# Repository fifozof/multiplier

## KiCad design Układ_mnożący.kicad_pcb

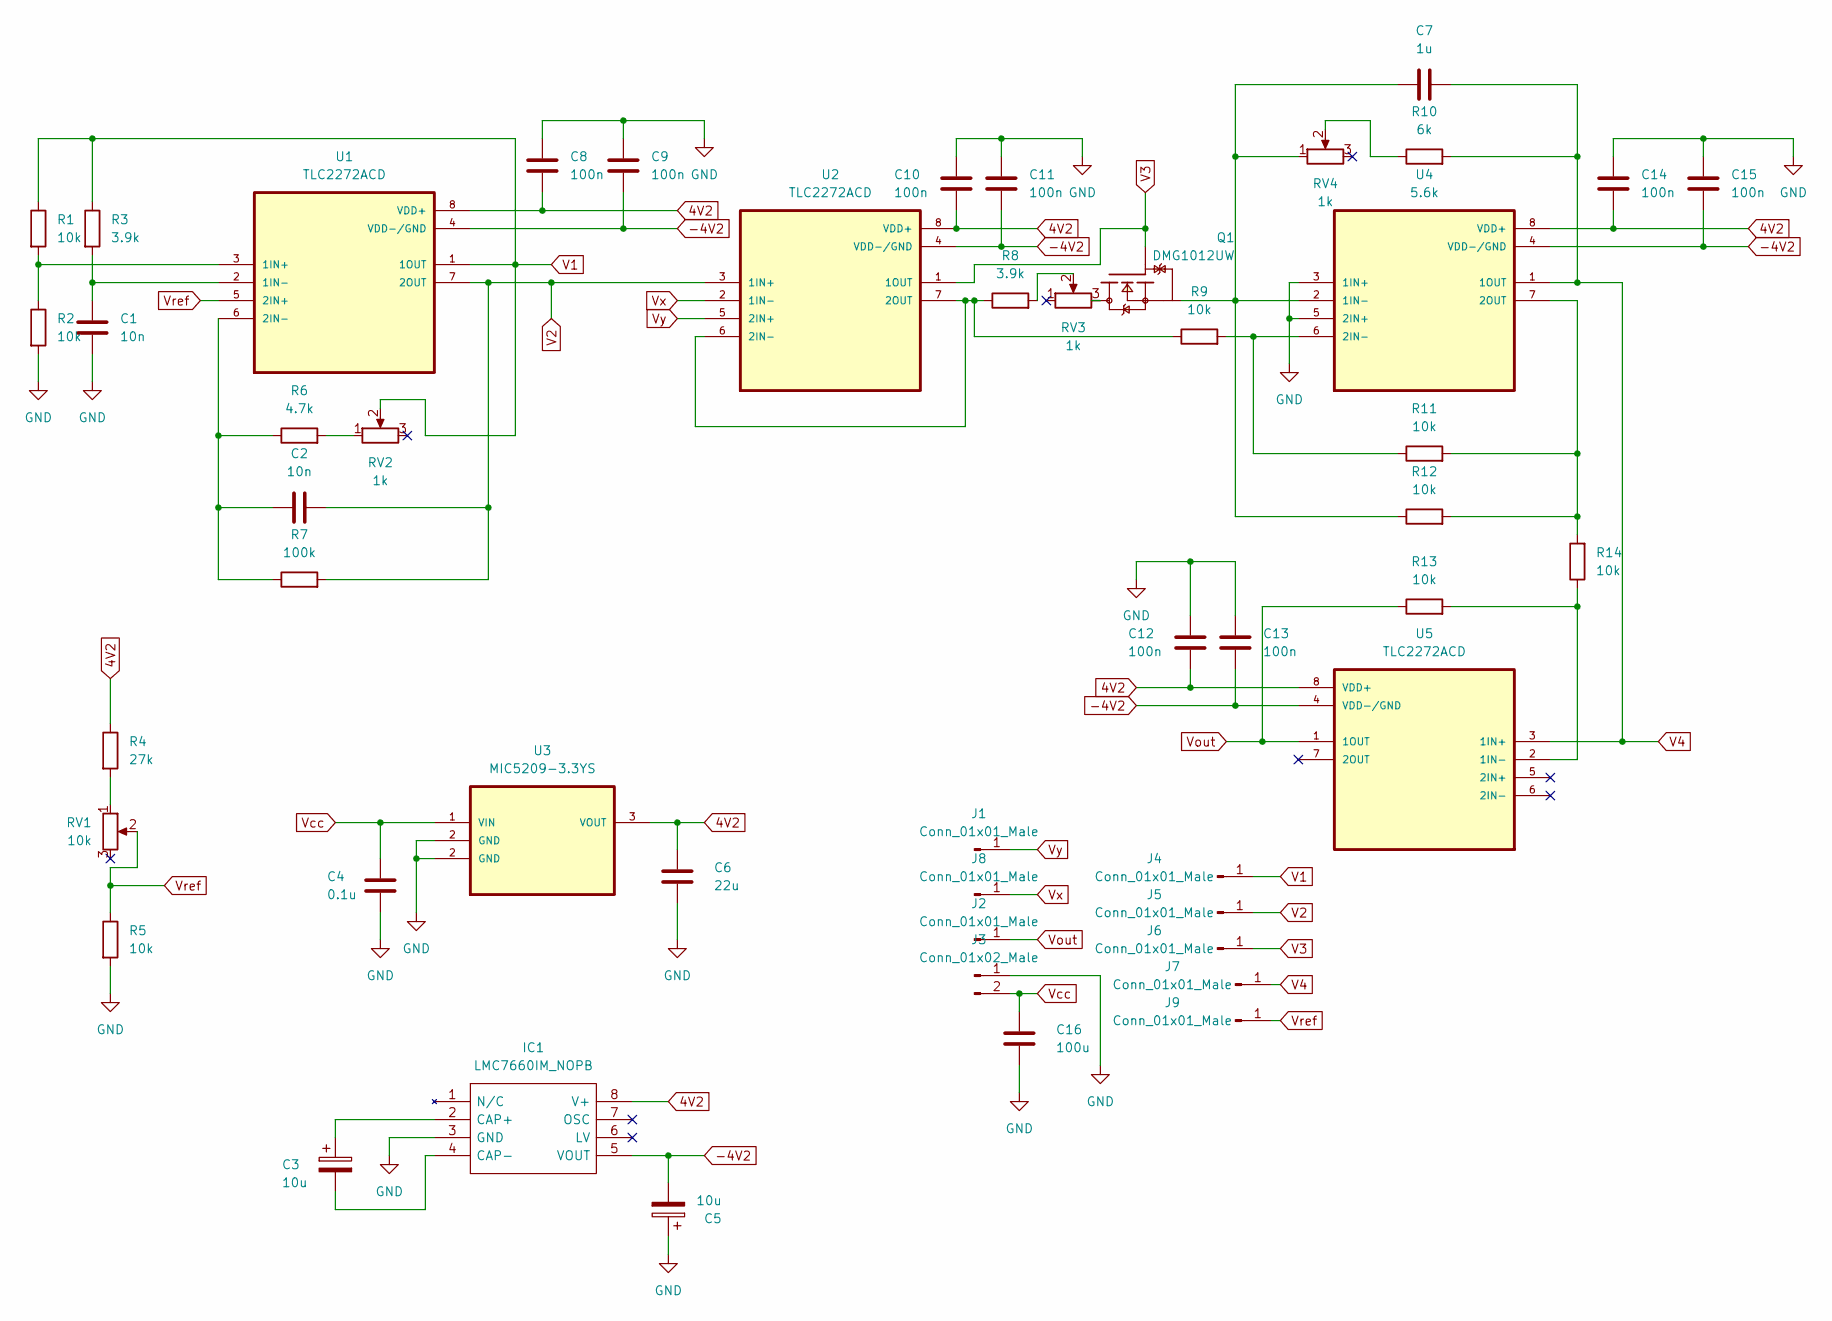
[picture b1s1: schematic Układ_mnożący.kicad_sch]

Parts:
C1, C2: 10n; C_0805_2012Metric_Pad1.18x1.45mm_HandSolder
C3, C5: 10u; C_1206_3216Metric_Pad1.33x1.80mm_HandSolder
C4: 0.1u; C_0805_2012Metric_Pad1.18x1.45mm_HandSolder
C6: 22u; CP_EIA-3528-21_Kemet-B
C7: 1u; C_0805_2012Metric_Pad1.18x1.45mm_HandSolder
C8, C9, C10, C11, C12, C13, C14, C15: 100n; C_0805_2012Metric_Pad1.18x1.45mm_HandSolder
C16: 100u; CP_EIA-3528-21_Kemet-B
IC1: LMC7660IM_NOPB; SOIC127P600X175-8N; Mouser Part Number 926-LMC7660IM/NOPB
J1, J2, J4, J5, J6, J7, J8, J9: Conn_01x01_Male; PinHeader_1x01_P2.54mm_Vertical
J3: Conn_01x02_Male; PinHeader_1x02_P2.54mm_Vertical
Q1: DMG1012UW; SOT323
R1, R2, R5, R9, R11, R12, R13, R14: 10k; R_0805_2012Metric_Pad1.20x1.40mm_HandSolder
R3, R8: 3.9k; R_0805_2012Metric_Pad1.20x1.40mm_HandSolder
R4: 27k; R_0805_2012Metric_Pad1.20x1.40mm_HandSolder
R6: 4.7k; R_0805_2012Metric_Pad1.20x1.40mm_HandSolder
R7: 100k; R_0805_2012Metric_Pad1.20x1.40mm_HandSolder
R10: 6k; R_0805_2012Metric_Pad1.20x1.40mm_HandSolder
RV1: 10k; Potentiometer_ACP_CA6-H2,5_Horizontal
RV2, RV3, RV4: 1k; Potentiometer_ACP_CA6-H2,5_Horizontal
U1, U2, U5: TLC2272ACD; SOIC127P599X175-8N
U3: MIC5209-3.3YS; SOT-223-3_TabPin2
U4: 5.6k; SOIC127P599X175-8N

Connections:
4V2: C6.1, C8.2, C10.2, C12.2, C14.2, IC1.8 (V+), R4.1, U1.8 (VDD+), U2.8 (VDD+), U3.3 (VOUT), U4.8 (VDD+), U5.8 (VDD+)
-4V2: C5.2, C9.2, C11.2, C13.2, C15.2, IC1.5 (VOUT), U1.4 (VDD-/GND), U2.4 (VDD-/GND), U4.4 (VDD-/GND), U5.4 (VDD-/GND)
GND: C1.2, C4.2, C5.1, C6.2, C8.1, C9.1, C10.1, C11.1, C12.1, C13.1, C14.1, C15.1, C16.2, IC1.3 (GND), J3.1, R2.2, R5.2, U3.2 (GND), U4.3 (1IN+), U4.5 (2IN+)
unnamed: C1.1, R3.2, U1.2 (1IN-)
unnamed: C2.1, R6.1, R7.1, U1.6 (2IN-)
unnamed: C3.1, IC1.2 (CAP+)
unnamed: C3.2, IC1.4 (CAP-)
unnamed: C7.1, Q1.3, R12.1, RV4.1, U4.2 (1IN-)
unnamed: Q1.1, RV3.3
unnamed: R1.2, R2.1, U1.3 (1IN+)
unnamed: R4.2, RV1.1
unnamed: R6.2, RV2.1
unnamed: R8.1, R9.1, U2.6 (2IN-), U2.7 (2OUT)
unnamed: R8.2, RV3.2
unnamed: R10.1, RV4.2
unnamed: R9.2, R11.1, U4.6 (2IN-)
unnamed: R11.2, R12.2, R14.2, U4.7 (2OUT)
unnamed: R13.2, R14.1, U5.2 (1IN-)
V1: J4.1, R1.1, R3.1, RV2.2, U1.1 (1OUT)
V2: C2.2, J5.1, R7.2, U1.7 (2OUT), U2.3 (1IN+)
V3: J6.1, Q1.2, U2.1 (1OUT)
V4: C7.2, J7.1, R10.2, U4.1 (1OUT), U5.3 (1IN+)
Vcc: C4.1, C16.1, J3.2, U3.1 (VIN)
Vout: J2.1, R13.1, U5.1 (1OUT)
Vref: J9.1, R5.1, RV1.2, U1.5 (2IN+)
Vx: J8.1, U2.2 (1IN-)
Vy: J1.1, U2.5 (2IN+)

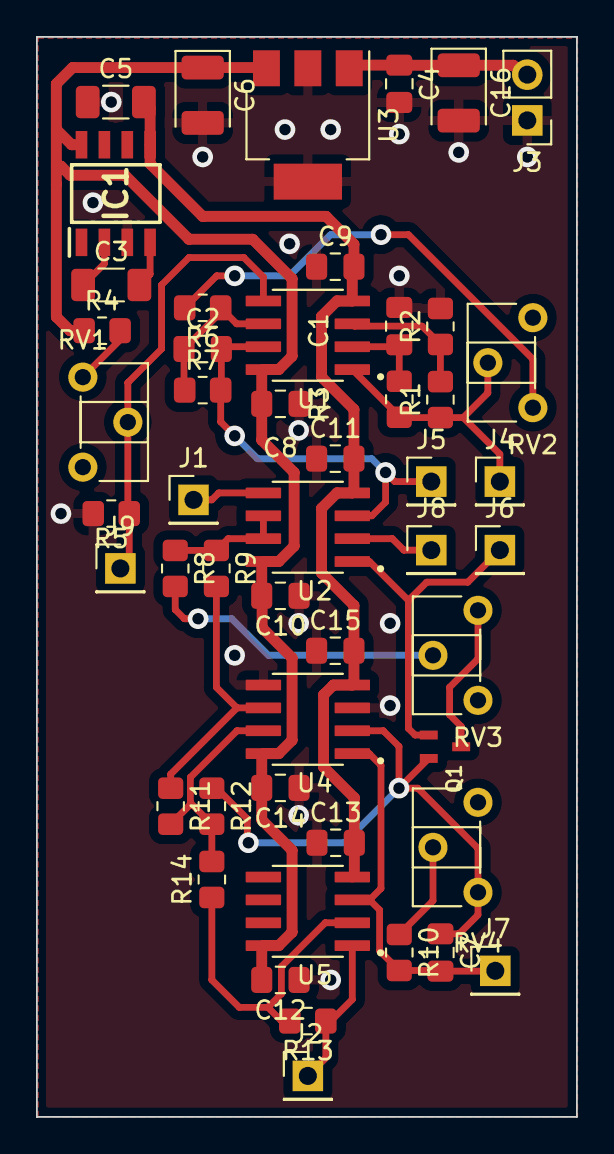
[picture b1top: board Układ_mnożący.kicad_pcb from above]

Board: 2 copper layers, 30.0 x 60.0 mm, 50 parts (0 on the bottom side), 27 nets.

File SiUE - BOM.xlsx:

Item | Qty | Reference(s) | Value | LibPart | Footprint | Manufacturer_Name | Manufacturer_Part_Number | TME link
1 | 1 | C1 | 10n | Device:C | Capacitor_SMD:C_0805_2012Metric_Pad1.18x1.45mm_HandSolder
2 | 2 | C2, C7 | C | Device:C | Capacitor_SMD:C_0805_2012Metric_Pad1.18x1.45mm_HandSolder
3 | 2 | C3, C5 | 10u | Device:C_Polarized | Capacitor_THT:CP_Radial_D12.5mm_P5.00mm
4 | 1 | C4 | 0.1u | Device:C | Capacitor_SMD:C_0805_2012Metric_Pad1.18x1.45mm_HandSolder
5 | 1 | C6 | 22u | Device:C | Capacitor_SMD:C_1206_3216Metric_Pad1.33x1.80mm_HandSolder | VISHAY | 293D226X9010A2TE3 | 293D226X9010A2TE3 VISHAY - Kondensator: tantalowy | 22uF; 10VDC; SMD; A; 1206; 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
6 | 1 | IC1 | LMC7660IM_NOPB | LMC7660IM_NOPB:LMC7660IM_NOPB | LMC7660IM_NOPB:SOIC127P600X175-8N | Texas Instruments | LMC7660IM/NOPB
7 | 1 | J1 | Conn_01x02_Male | Connector:Conn_01x02_Male | Connector_PinHeader_2.54mm:PinHeader_1x02_P2.54mm_Vertical
8 | 2 | J2, J3 | Conn_01x01_Male | Connector:Conn_01x01_Male | Connector_PinHeader_2.54mm:PinHeader_1x01_P2.54mm_Vertical
9 | 1 | Q1 | DMG1012UW | DMG1012UW:DMG1012UW | DMG1012UW:SOT323 | DIODES INCORPORATED | DMG1012UW-7 | DMG1012UW-7 DIODES INCORPORATED - Tranzystor: N-MOSFET | unipolarny; 20V; 1A; 0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
10 | 8 | R1, R2, R5, R9, R11, R12, R13, R14 | 10k | Device:R | Resistor_SMD:R_0805_2012Metric_Pad1.20x1.40mm_HandSolder
11 | 1 | R3 | 3.9k | Device:R | Resistor_SMD:R_0805_2012Metric_Pad1.20x1.40mm_HandSolder
12 | 1 | R4 | 27k | Device:R | Resistor_SMD:R_0805_2012Metric_Pad1.20x1.40mm_HandSolder
13 | 2 | R6, R8 | 4.7k | Device:R | Resistor_SMD:R_0805_2012Metric_Pad1.20x1.40mm_HandSolder
14 | 2 | R7, R10 | R | Device:R | Resistor_SMD:R_0805_2012Metric_Pad1.20x1.40mm_HandSolder
15 | 1 | RV1 | 10k | Device:R_Potentiometer | Potentiometer_SMD:Potentiometer_Bourns_3214G_Horizontal
16 | 3 | RV2, RV3, RV4 | R_Potentiometer | Device:R_Potentiometer | Potentiometer_SMD:Potentiometer_Bourns_3214G_Horizontal | SR PASSIVES | 3305SMD | 3305SMD-1K SR PASSIVES - Potencjometr: montażowy | jednoobrotowy; 1kΩ; 100mW; S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
17 | 4 | U1, U2, U4, U5 | TLC2272ACD | TLC2272ACD:TLC2272ACD | TLC2272ACD:SOIC127P599X175-8N | TEXAS INSTRUMENTS | TLC2272ACD | TLC2272ACD TEXAS INSTRUMENTS - IC: wzmacniacz operacyjny | 2,18MHz; Ch: 2; SO8 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
18 | 1 | U3 | MIC5209-4.2YS | mic5209-4.2ys:MIC5209-4.2YS | Package_TO_SOT_SMD:SOT-223-3_TabPin2 | MICROCHIP | MIC5209-4.2YS | MIC5209-4.2YS MICROCHIP (MICREL) - IC: stabilizator napięcia | LDO,liniowy,nier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

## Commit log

2022-11-15 Final electrical schematic
2022-11-15 Final Electrical Schematic v2
    Added pinout to Vref
2022-11-19 Final PCB design
2022-11-20 Final PCB design v2
